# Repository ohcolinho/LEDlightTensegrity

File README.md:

LEDlightTensegrity
==================
Using Kicad Libraries from
https://github.com/0xANDREW/kicad-libs

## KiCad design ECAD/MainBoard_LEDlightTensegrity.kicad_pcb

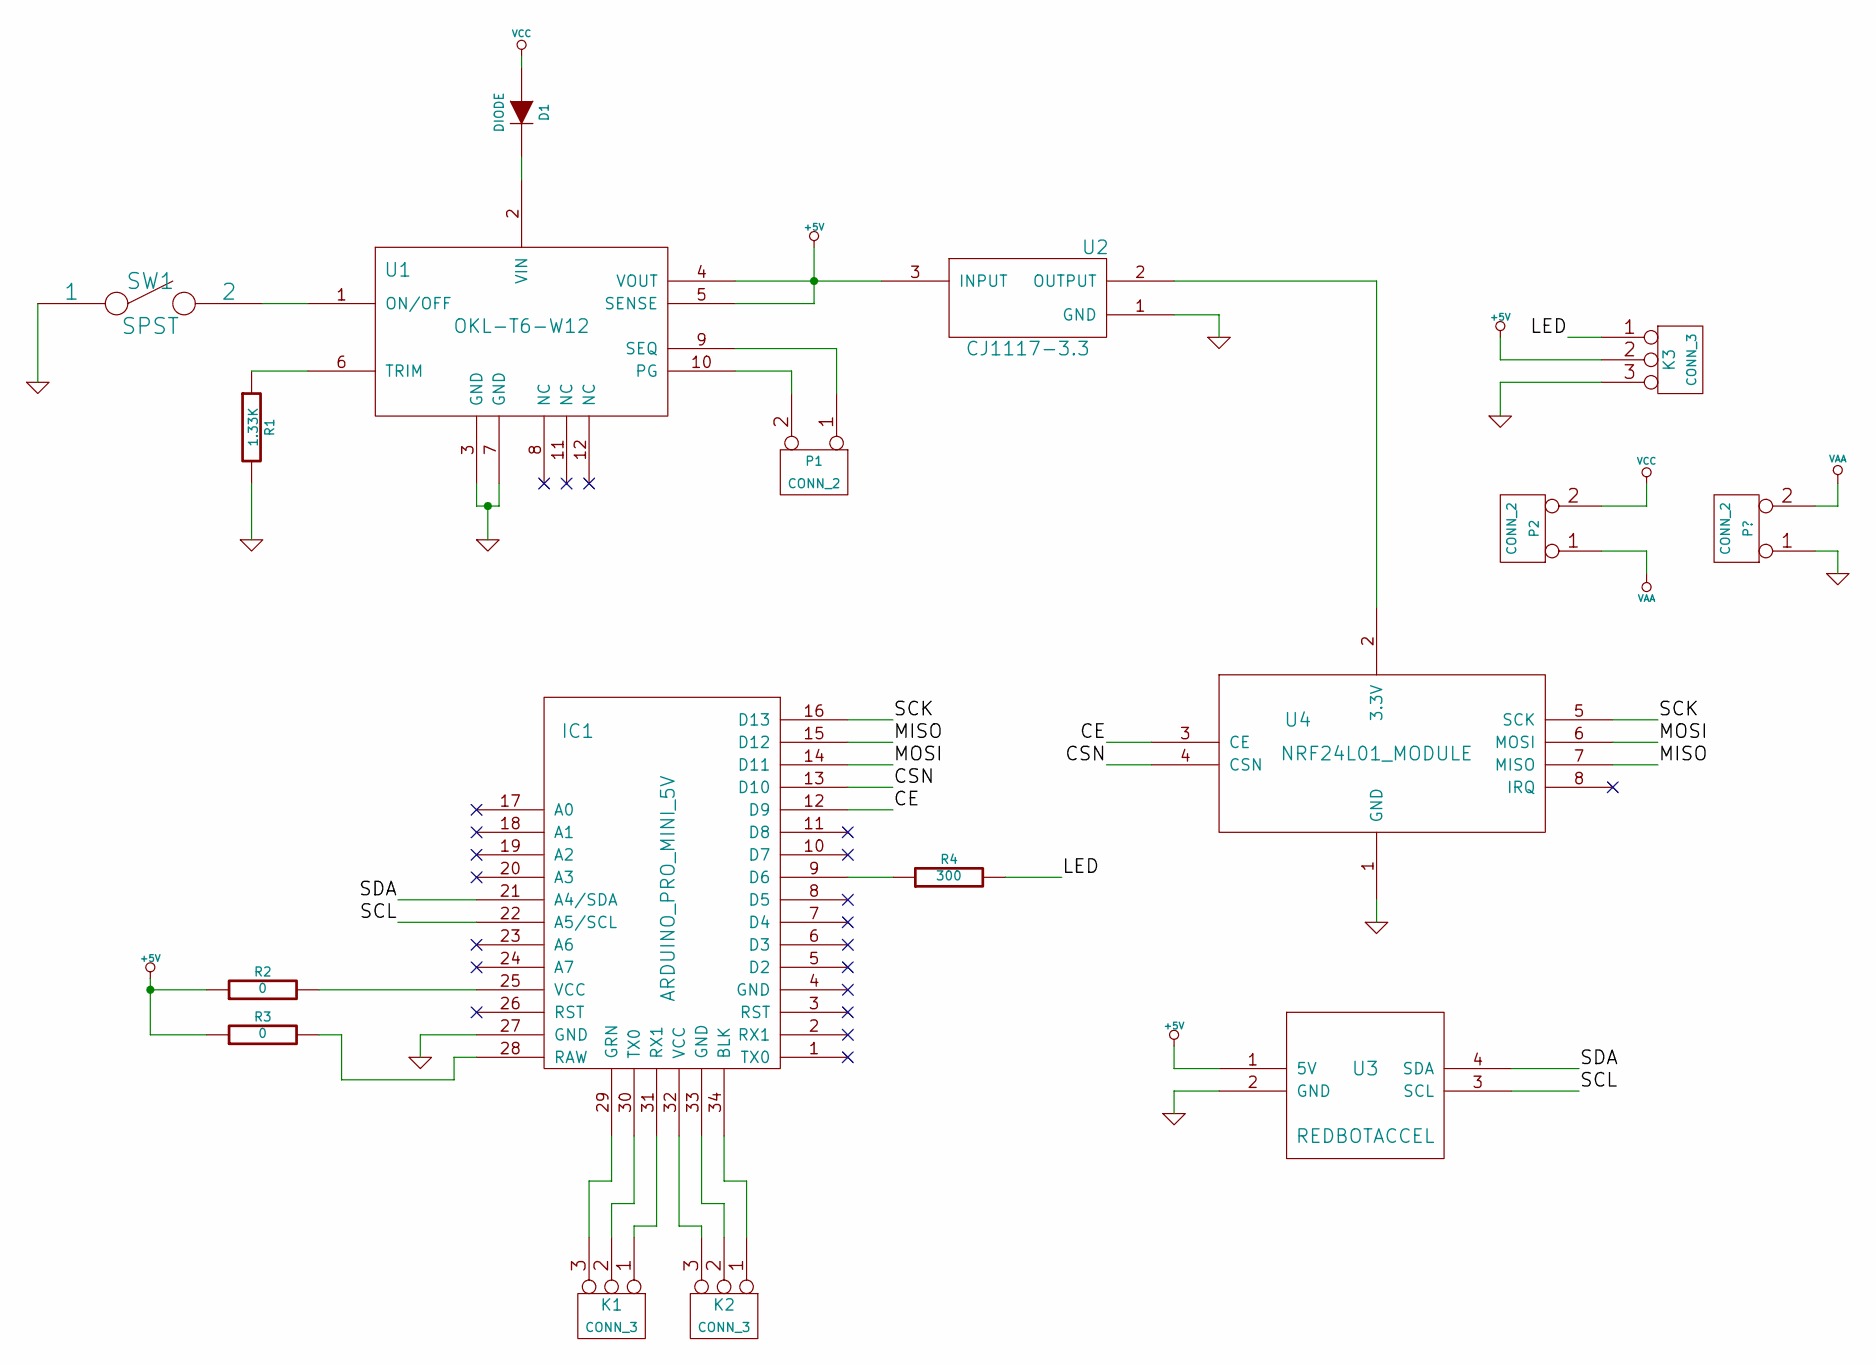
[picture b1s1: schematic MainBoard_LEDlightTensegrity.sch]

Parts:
D1: DIODE
IC1: ARDUINO_PRO_MINI_5V
K1, K2, K3: CONN_3
P1, P2: CONN_2
R1: 1.33K
R2, R3: 0
R4: 300
SW1: SPST
U1: OKL-T6-W12
U2: CJ1117-3.3
U3: REDBOTACCEL
U4: NRF24L01_MODULE

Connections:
+5V: K3.2 (PM), R2.1, R3.1, U1.4 (VOUT), U1.5 (SENSE), U2.3 (INPUT), U3.1 (5V)
/CE: IC1.12 (D9), U4.3 (CE)
/CSN: IC1.13 (D10), U4.4 (CSN)
/LED: K3.1, R4.2
/MISO: IC1.15 (D12), U4.7 (MISO)
/MOSI: IC1.14 (D11), U4.6 (MOSI)
/SCK: IC1.16 (D13), U4.5 (SCK)
/SCL: IC1.22 (A5/SCL), U3.3 (SCL)
/SDA: IC1.21 (A4/SDA), U3.4 (SDA)
GND: IC1.27 (GND), K3.3, R1.2, SW1.1, U1.3 (GND), U1.7 (GND), U2.1 (GND), U3.2 (GND), U4.1 (GND); also elsewhere on the board
unnamed: IC1.9 (D6), R4.1
unnamed: R1.1, U1.6 (TRIM)
unnamed: IC1.31 (RX1), K1.1
unnamed: IC1.32 (VCC), K2.3
unnamed: IC1.33 (GND), K2.2 (PM)
unnamed: IC1.34 (BLK), K2.1
unnamed: SW1.2, U1.1 (ON/OFF)
unnamed: D1.2 (K), U1.2 (VIN)
unnamed: U2.2 (OUTPUT), U4.2 (3.3V)
unnamed: P1.2 (PM), U1.10 (PG)
unnamed: P1.1, U1.9 (SEQ)
unnamed: IC1.25 (VCC), R2.2
unnamed: IC1.28 (RAW), R3.2
unnamed: IC1.29 (GRN), K1.3
unnamed: IC1.30 (TX0), K1.2 (PM)
VAA: P2.1; also elsewhere on the board
VCC: D1.1 (A), P2.2 (PM)

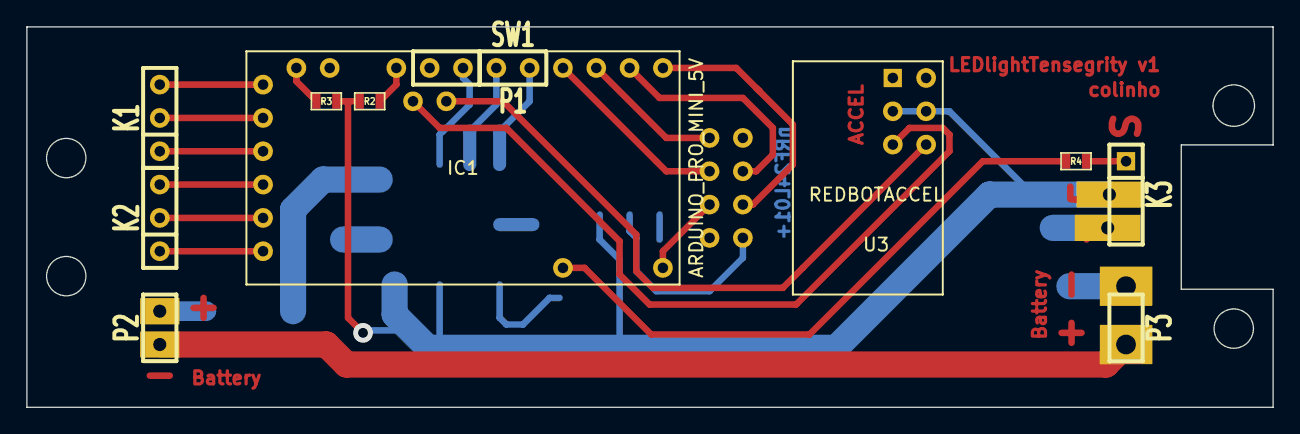
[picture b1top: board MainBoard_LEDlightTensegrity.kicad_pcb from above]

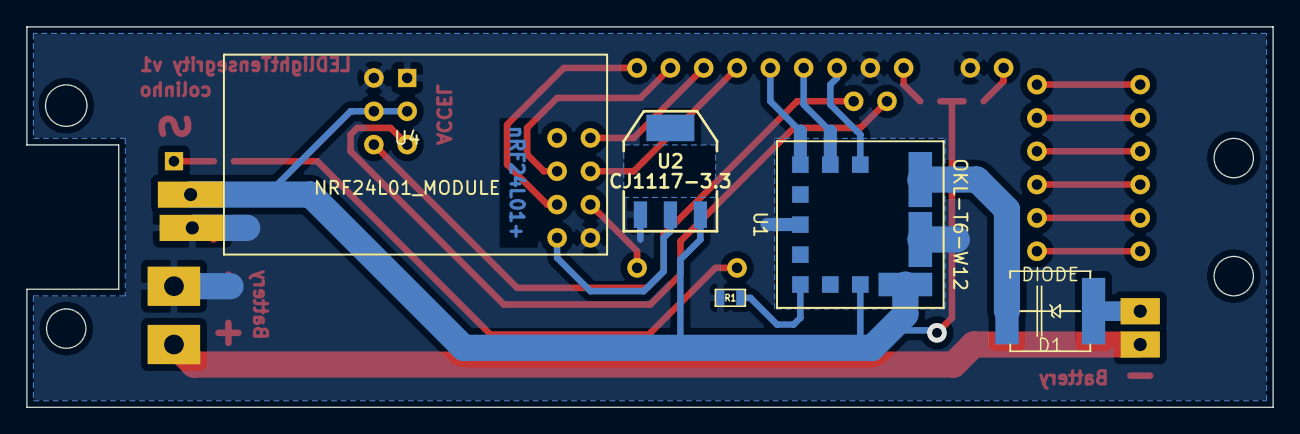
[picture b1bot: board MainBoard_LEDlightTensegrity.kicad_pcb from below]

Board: 2 copper layers, 95.0 x 29.0 mm, 17 parts (5 on the bottom side), 27 nets.

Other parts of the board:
P3: CONN_2; SIL-2

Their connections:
GND: P3.1; also elsewhere on the board
VAA: P3.2; also elsewhere on the board

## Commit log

2014-08-28 Added initial schematic and component libraries
    made schematic components for nRF, RedBot Accel, and OKL switching
    regulator (all in custom.lib). Modified Arduino Mini Pro schematic
    component
2014-08-29 added LDO to schematic and made library component
    Added CJ1117-3.3 LDO from SeeedStudio's Open Parts Library
2014-08-29 First Version of Schematic Complete
    Generated Netlist
2014-08-30 Finished Layout
2014-08-31 Added Protection Diode and Secondary Battery Path
    Added Reverse Voltage Protection Diode. Also added second battery input
    if only two batteries are used vs 4 total (2x on each side). Added
    footprint for diode DO-214AB
2014-09-02 Added updated Gerbers
2014-09-03 Changed drills to sizes for LPKF board mill
    LPKF board mill doesn't have 0.85mm drill, KiCAD vias are 0.85mm
    standard. Drove me crazy trying to find it...
2014-09-03 Changed outer cut for structural mounting
    Extended board cuts so it can be mounted to 3D printed brackets
2014-09-03 added Gerbers for new version with extended outline
    also added screen capture of layout
2014-09-11 Added first push of Arduino control code
    Simple Accelerometer + lights responding code to test tube segments
2014-09-16 added rev4 with tilt sensing w/ averaging
2014-09-17 added code5 -
    added smoothed mode switching
    added push-pull pulsing patch
    added tilt color mapping
2014-09-18 added spring up patch
    bi-direction working - added tiltDir variable to track which side is up
2014-09-19 updated code with autoshutoff
    autoshutoff after 13min, 3min shutoff if no activity (temporary)
    v9 is code being used in Thursday night performance
